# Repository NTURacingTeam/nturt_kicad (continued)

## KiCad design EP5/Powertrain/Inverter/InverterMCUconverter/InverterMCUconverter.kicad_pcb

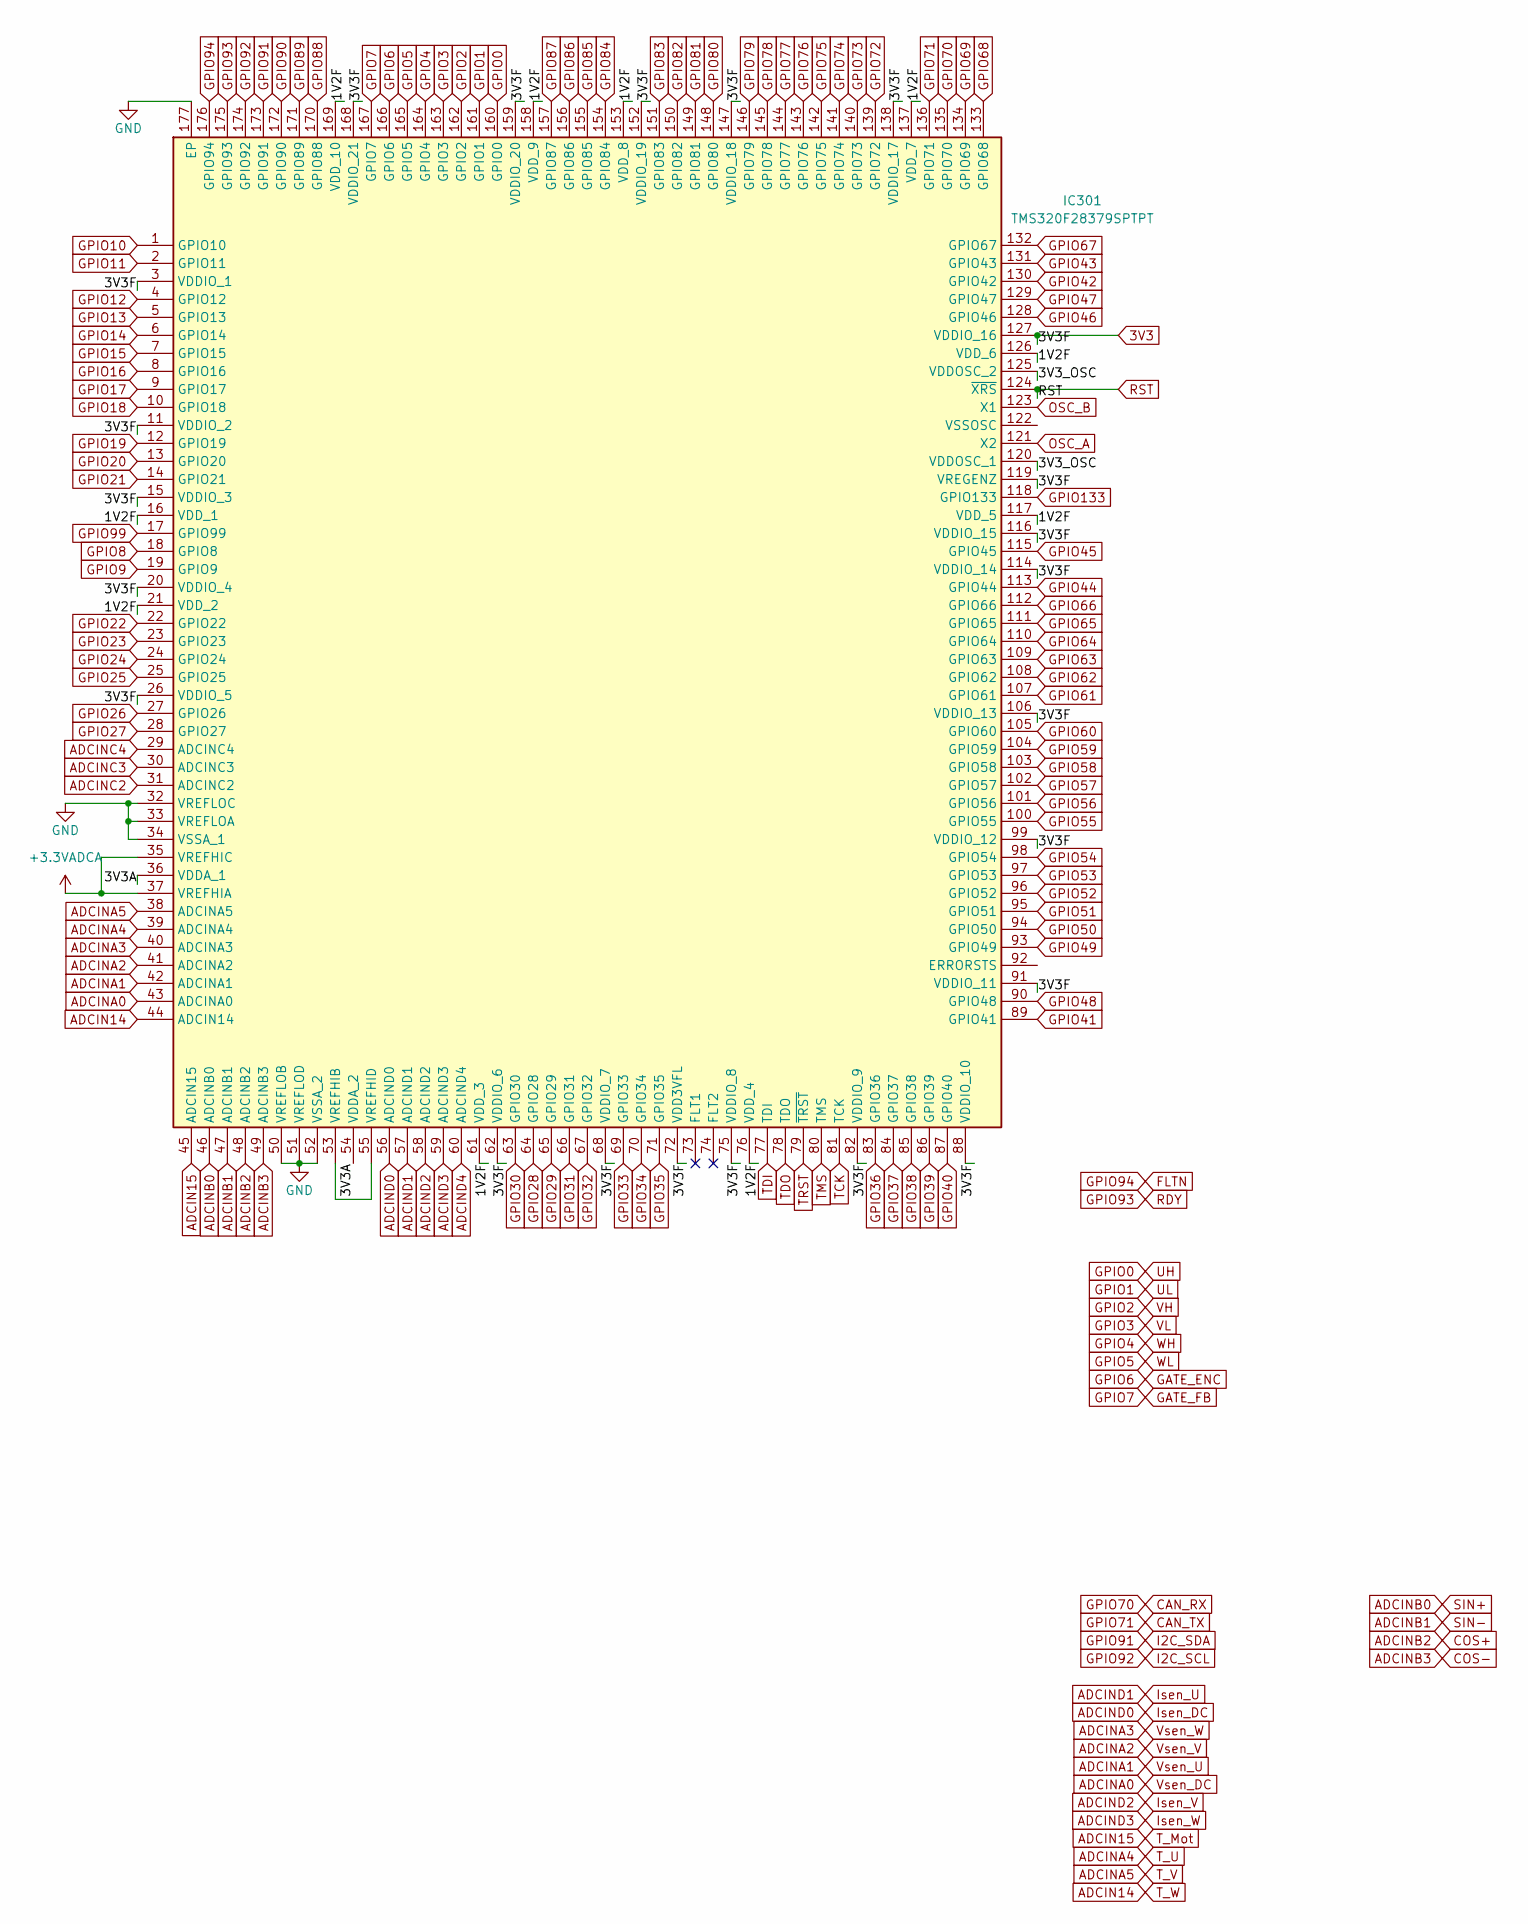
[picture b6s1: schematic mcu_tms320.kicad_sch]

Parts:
IC301: TMS320F28379SPTPT; QFP50P2600X2600X160-177N; Mouser Part Number 595-TMS32028379SPTPT

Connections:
3V3: IC301.3 (VDDIO_1), IC301.11 (VDDIO_2), IC301.15 (VDDIO_3), IC301.20 (VDDIO_4), IC301.26 (VDDIO_5), IC301.62 (VDDIO_6), IC301.68 (VDDIO_7), IC301.72 (VDD3VFL), IC301.75 (VDDIO_8), IC301.82 (VDDIO_9), IC301.88 (VDDIO_10), IC301.91 (VDDIO_11), IC301.99 (VDDIO_12), IC301.106 (VDDIO_13), IC301.114 (VDDIO_14), IC301.116 (VDDIO_15), IC301.119 (VREGENZ), IC301.127 (VDDIO_16), IC301.138 (VDDIO_17), IC301.147 (VDDIO_18), IC301.152 (VDDIO_19), IC301.159 (VDDIO_20), IC301.168 (VDDIO_21); also elsewhere on the board
+3.3VADCA: IC301.35 (VREFHIC), IC301.37 (VREFHIA)
/TMS320/1V2F: IC301.16 (VDD_1), IC301.21 (VDD_2), IC301.61 (VDD_3), IC301.76 (VDD_4), IC301.117 (VDD_5), IC301.126 (VDD_6), IC301.137 (VDD_7), IC301.153 (VDD_8), IC301.158 (VDD_9), IC301.169 (VDD_10)
/TMS320/3V3A: IC301.36 (VDDA_1), IC301.54 (VDDA_2)
/TMS320/3V3_OSC: IC301.120 (VDDOSC_1), IC301.125 (VDDOSC_2)
ADCIN14: IC301.44 (ADCIN14); also elsewhere on the board
ADCIN15: IC301.45 (ADCIN15); also elsewhere on the board
ADCINA0: IC301.43 (ADCINA0); also elsewhere on the board
ADCINA1: IC301.42 (ADCINA1); also elsewhere on the board
ADCINA2: IC301.41 (ADCINA2); also elsewhere on the board
ADCINA3: IC301.40 (ADCINA3); also elsewhere on the board
ADCINA4: IC301.39 (ADCINA4); also elsewhere on the board
ADCINA5: IC301.38 (ADCINA5); also elsewhere on the board
ADCINB0: IC301.46 (ADCINB0)
ADCINB1: IC301.47 (ADCINB1)
ADCINB2: IC301.48 (ADCINB2)
ADCINB3: IC301.49 (ADCINB3)
ADCINC2: IC301.31 (ADCINC2)
ADCINC3: IC301.30 (ADCINC3)
ADCINC4: IC301.29 (ADCINC4)
ADCIND0: IC301.56 (ADCIND0); also elsewhere on the board
ADCIND1: IC301.57 (ADCIND1); also elsewhere on the board
ADCIND2: IC301.58 (ADCIND2); also elsewhere on the board
ADCIND3: IC301.59 (ADCIND3); also elsewhere on the board
ADCIND4: IC301.60 (ADCIND4)
CAN_RX: IC301.135 (GPIO70); also elsewhere on the board
CAN_TX: IC301.136 (GPIO71); also elsewhere on the board
FLTN: IC301.176 (GPIO94); also elsewhere on the board
GATE_ENC: IC301.166 (GPIO6); also elsewhere on the board
GATE_FB: IC301.167 (GPIO7); also elsewhere on the board
GND: IC301.32 (VREFLOC), IC301.33 (VREFLOA), IC301.34 (VSSA_1), IC301.50 (VREFLOB), IC301.51 (VREFLOD), IC301.52 (VSSA_2), IC301.177 (EP); also elsewhere on the board
GPIO0: IC301.160 (GPIO0); also elsewhere on the board
GPIO1: IC301.161 (GPIO1); also elsewhere on the board
GPIO2: IC301.162 (GPIO2); also elsewhere on the board
GPIO3: IC301.163 (GPIO3); also elsewhere on the board
GPIO4: IC301.164 (GPIO4); also elsewhere on the board
GPIO5: IC301.165 (GPIO5); also elsewhere on the board
GPIO8: IC301.18 (GPIO8)
GPIO9: IC301.19 (GPIO9)
GPIO10: IC301.1 (GPIO10)
GPIO11: IC301.2 (GPIO11)
GPIO12: IC301.4 (GPIO12)
GPIO13: IC301.5 (GPIO13)
GPIO14: IC301.6 (GPIO14)
GPIO15: IC301.7 (GPIO15)
GPIO16: IC301.8 (GPIO16)
GPIO17: IC301.9 (GPIO17)
GPIO18: IC301.10 (GPIO18)
GPIO19: IC301.12 (GPIO19)
GPIO20: IC301.13 (GPIO20)
GPIO21: IC301.14 (GPIO21)
GPIO22: IC301.22 (GPIO22)
GPIO23: IC301.23 (GPIO23)
GPIO24: IC301.24 (GPIO24)
GPIO25: IC301.25 (GPIO25)
GPIO26: IC301.27 (GPIO26)
GPIO27: IC301.28 (GPIO27)
GPIO28: IC301.64 (GPIO28)
GPIO29: IC301.65 (GPIO29)
GPIO30: IC301.63 (GPIO30)
GPIO31: IC301.66 (GPIO31)
GPIO32: IC301.67 (GPIO32)
GPIO33: IC301.69 (GPIO33)
GPIO34: IC301.70 (GPIO34)
GPIO35: IC301.71 (GPIO35)
GPIO36: IC301.83 (GPIO36)
GPIO37: IC301.84 (GPIO37)
GPIO38: IC301.85 (GPIO38)
GPIO39: IC301.86 (GPIO39)
GPIO40: IC301.87 (GPIO40)
GPIO41: IC301.89 (GPIO41)
GPIO42: IC301.130 (GPIO42)
GPIO43: IC301.131 (GPIO43)
GPIO44: IC301.113 (GPIO44)
GPIO45: IC301.115 (GPIO45)
GPIO46: IC301.128 (GPIO46)
GPIO47: IC301.129 (GPIO47)
GPIO48: IC301.90 (GPIO48)
GPIO49: IC301.93 (GPIO49)
GPIO50: IC301.94 (GPIO50)
GPIO51: IC301.95 (GPIO51)
GPIO52: IC301.96 (GPIO52)
GPIO53: IC301.97 (GPIO53)
GPIO54: IC301.98 (GPIO54)
GPIO55: IC301.100 (GPIO55)
GPIO56: IC301.101 (GPIO56)
GPIO57: IC301.102 (GPIO57)
GPIO58: IC301.103 (GPIO58)
GPIO59: IC301.104 (GPIO59)
GPIO60: IC301.105 (GPIO60)
GPIO61: IC301.107 (GPIO61)
GPIO62: IC301.108 (GPIO62)
GPIO63: IC301.109 (GPIO63)
GPIO64: IC301.110 (GPIO64)
GPIO65: IC301.111 (GPIO65)
GPIO66: IC301.112 (GPIO66)
GPIO67: IC301.132 (GPIO67)
GPIO68: IC301.133 (GPIO68)
GPIO69: IC301.134 (GPIO69)
GPIO72: IC301.139 (GPIO72)
GPIO73: IC301.140 (GPIO73)
GPIO74: IC301.141 (GPIO74)
GPIO75: IC301.142 (GPIO75)
GPIO76: IC301.143 (GPIO76)
GPIO77: IC301.144 (GPIO77)
GPIO78: IC301.145 (GPIO78)
GPIO79: IC301.146 (GPIO79)
GPIO80: IC301.148 (GPIO80)
GPIO81: IC301.149 (GPIO81)
GPIO82: IC301.150 (GPIO82)
GPIO83: IC301.151 (GPIO83)
GPIO84: IC301.154 (GPIO84)
GPIO85: IC301.155 (GPIO85)
GPIO86: IC301.156 (GPIO86)
GPIO87: IC301.157 (GPIO87)
GPIO88: IC301.170 (GPIO88)
GPIO89: IC301.171 (GPIO89)
GPIO90: IC301.172 (GPIO90)
GPIO91: IC301.173 (GPIO91); also elsewhere on the board
GPIO92: IC301.174 (GPIO92); also elsewhere on the board
GPIO93: IC301.175 (GPIO93); also elsewhere on the board
GPIO99: IC301.17 (GPIO99)
GPIO133: IC301.118 (GPIO133)
unnamed: IC301.53 (VREFHIB), IC301.55 (VREFHID)
OSC_A: IC301.121 (X2); also elsewhere on the board
OSC_B: IC301.123 (X1); also elsewhere on the board
RST: IC301.124 (~XRS)
TCK: IC301.81 (TCK)
TDI: IC301.77 (TDI)
TDO: IC301.78 (TDO)
TMS: IC301.80 (TMS)
TRST: IC301.79 (~TRST)

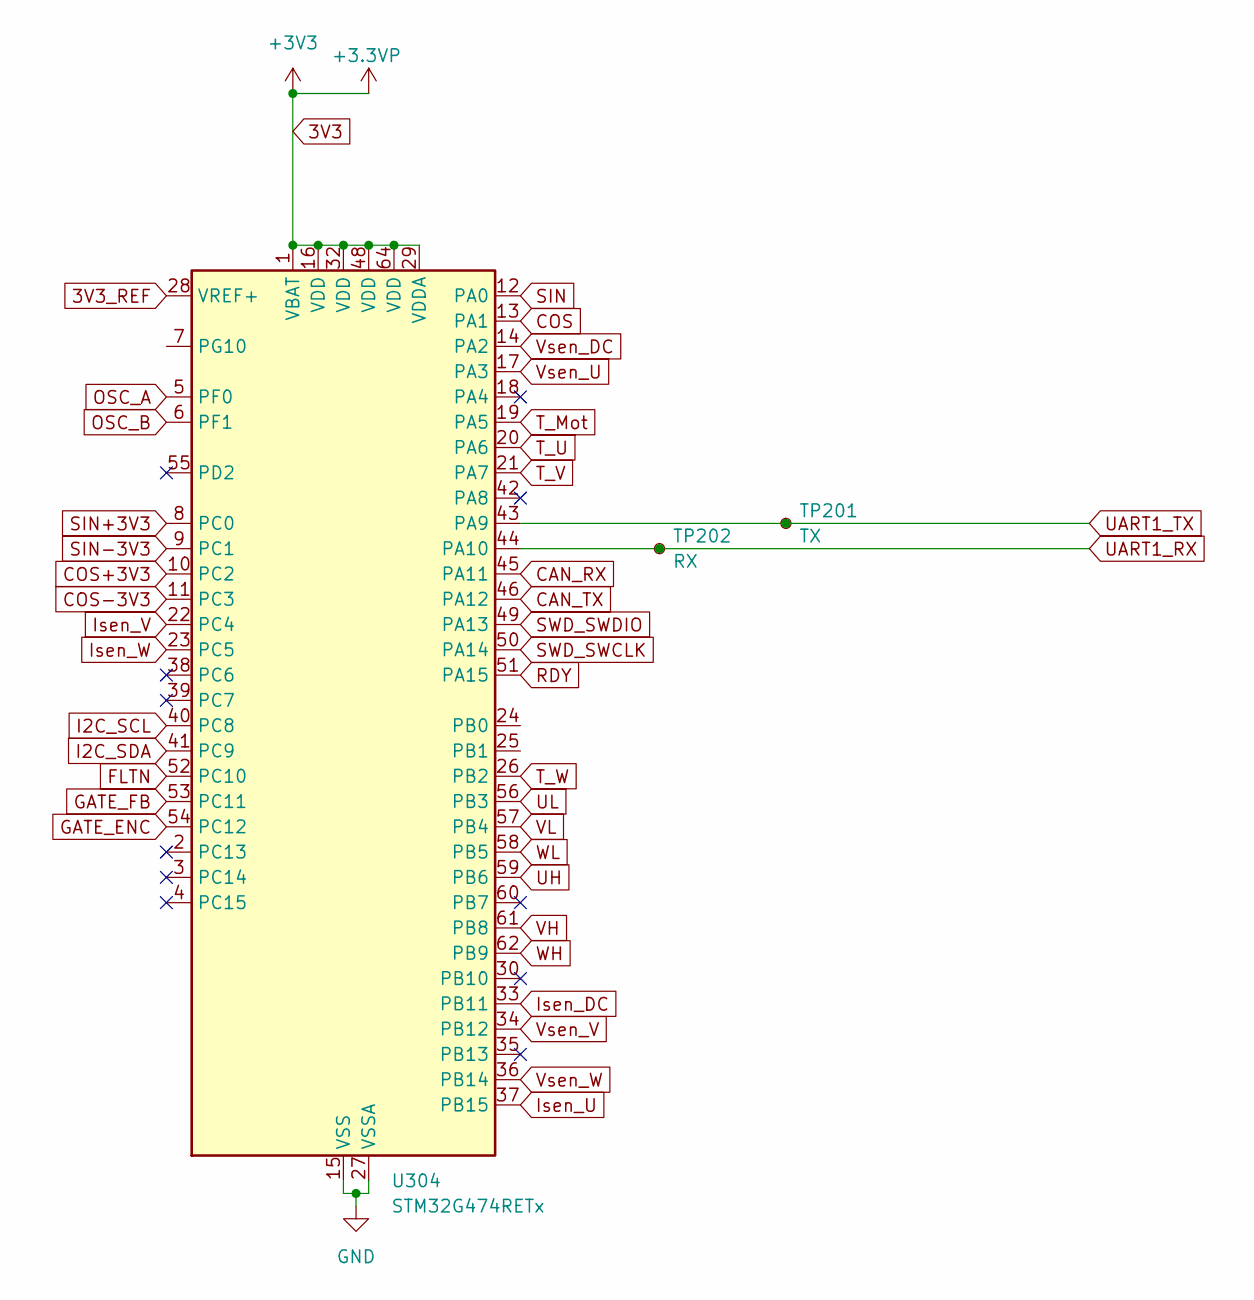
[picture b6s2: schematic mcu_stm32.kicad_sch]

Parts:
TP201: TX; TestPoint_Pad_D1.0mm
TP202: RX; TestPoint_Pad_D1.0mm
U304: STM32G474RETx; LQFP-64_10x10mm_P0.5mm

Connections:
3V3: U304.1 (VBAT), U304.16 (VDD), U304.29 (VDDA), U304.32 (VDD), U304.48 (VDD), U304.64 (VDD); also elsewhere on the board
3V3_REF: U304.28 (VREF+)
ADCIN14: U304.26 (PB2); also elsewhere on the board
ADCIN15: U304.19 (PA5); also elsewhere on the board
ADCINA0: U304.14 (PA2); also elsewhere on the board
ADCINA1: U304.17 (PA3); also elsewhere on the board
ADCINA2: U304.34 (PB12); also elsewhere on the board
ADCINA3: U304.36 (PB14); also elsewhere on the board
ADCINA4: U304.20 (PA6); also elsewhere on the board
ADCINA5: U304.21 (PA7); also elsewhere on the board
ADCIND0: U304.33 (PB11); also elsewhere on the board
ADCIND1: U304.37 (PB15); also elsewhere on the board
ADCIND2: U304.22 (PC4); also elsewhere on the board
ADCIND3: U304.23 (PC5); also elsewhere on the board
CAN_RX: U304.45 (PA11); also elsewhere on the board
CAN_TX: U304.46 (PA12); also elsewhere on the board
COS: U304.13 (PA1)
COS+3V3: U304.10 (PC2)
COS-3V3: U304.11 (PC3)
FLTN: U304.52 (PC10); also elsewhere on the board
GATE_ENC: U304.54 (PC12); also elsewhere on the board
GATE_FB: U304.53 (PC11); also elsewhere on the board
GND: U304.15 (VSS), U304.27 (VSSA), U304.31 (VSS), U304.47 (VSS), U304.63 (VSS); also elsewhere on the board
GPIO0: U304.59 (PB6); also elsewhere on the board
GPIO1: U304.56 (PB3); also elsewhere on the board
GPIO2: U304.61 (PB8); also elsewhere on the board
GPIO3: U304.57 (PB4); also elsewhere on the board
GPIO4: U304.62 (PB9); also elsewhere on the board
GPIO5: U304.58 (PB5); also elsewhere on the board
GPIO91: U304.41 (PC9); also elsewhere on the board
GPIO92: U304.40 (PC8); also elsewhere on the board
GPIO93: U304.51 (PA15); also elsewhere on the board
OSC_A: U304.5 (PF0); also elsewhere on the board
OSC_B: U304.6 (PF1); also elsewhere on the board
SIN: U304.12 (PA0)
SIN+3V3: U304.8 (PC0)
SIN-3V3: U304.9 (PC1)
SWD_SWCLK: U304.50 (PA14)
SWD_SWDIO: U304.49 (PA13)
UART1_RX: TP202.1, U304.44 (PA10)
UART1_TX: TP201.1, U304.43 (PA9)

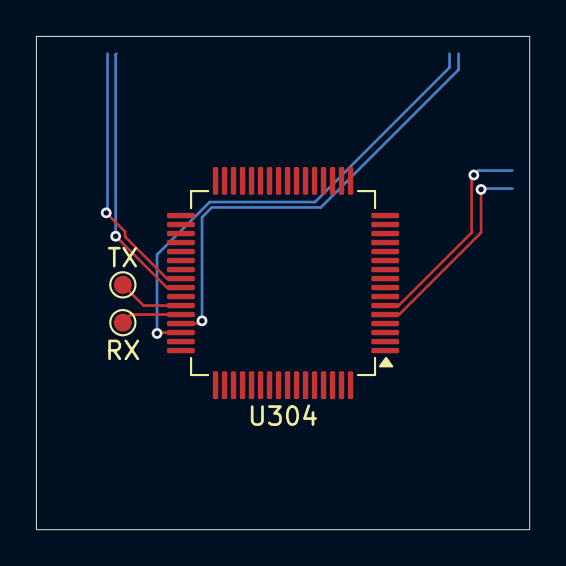
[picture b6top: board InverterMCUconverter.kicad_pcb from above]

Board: 2 copper layers, 27.4 x 27.4 mm, 4 parts (1 on the bottom side), 37 nets.

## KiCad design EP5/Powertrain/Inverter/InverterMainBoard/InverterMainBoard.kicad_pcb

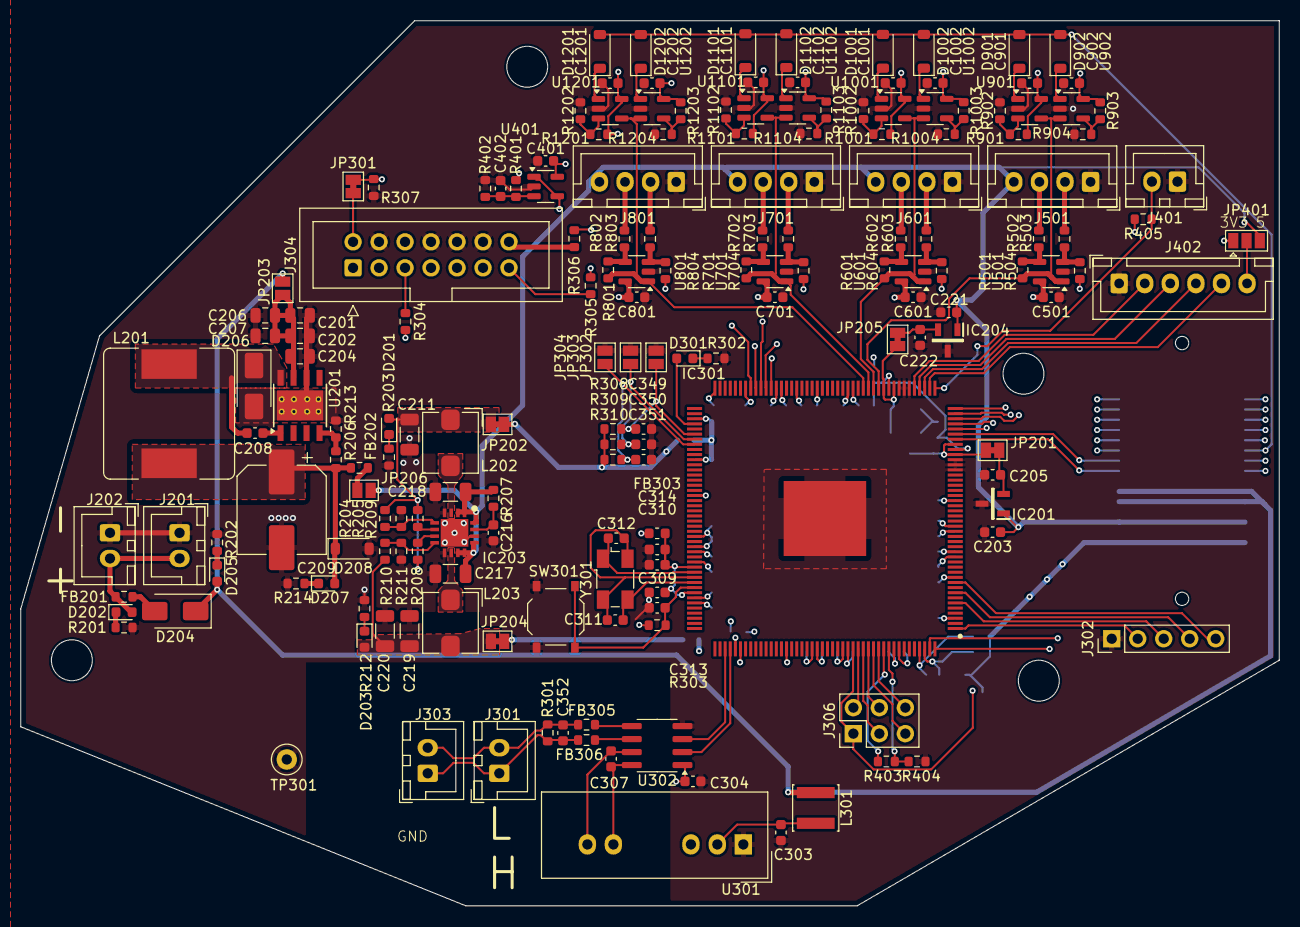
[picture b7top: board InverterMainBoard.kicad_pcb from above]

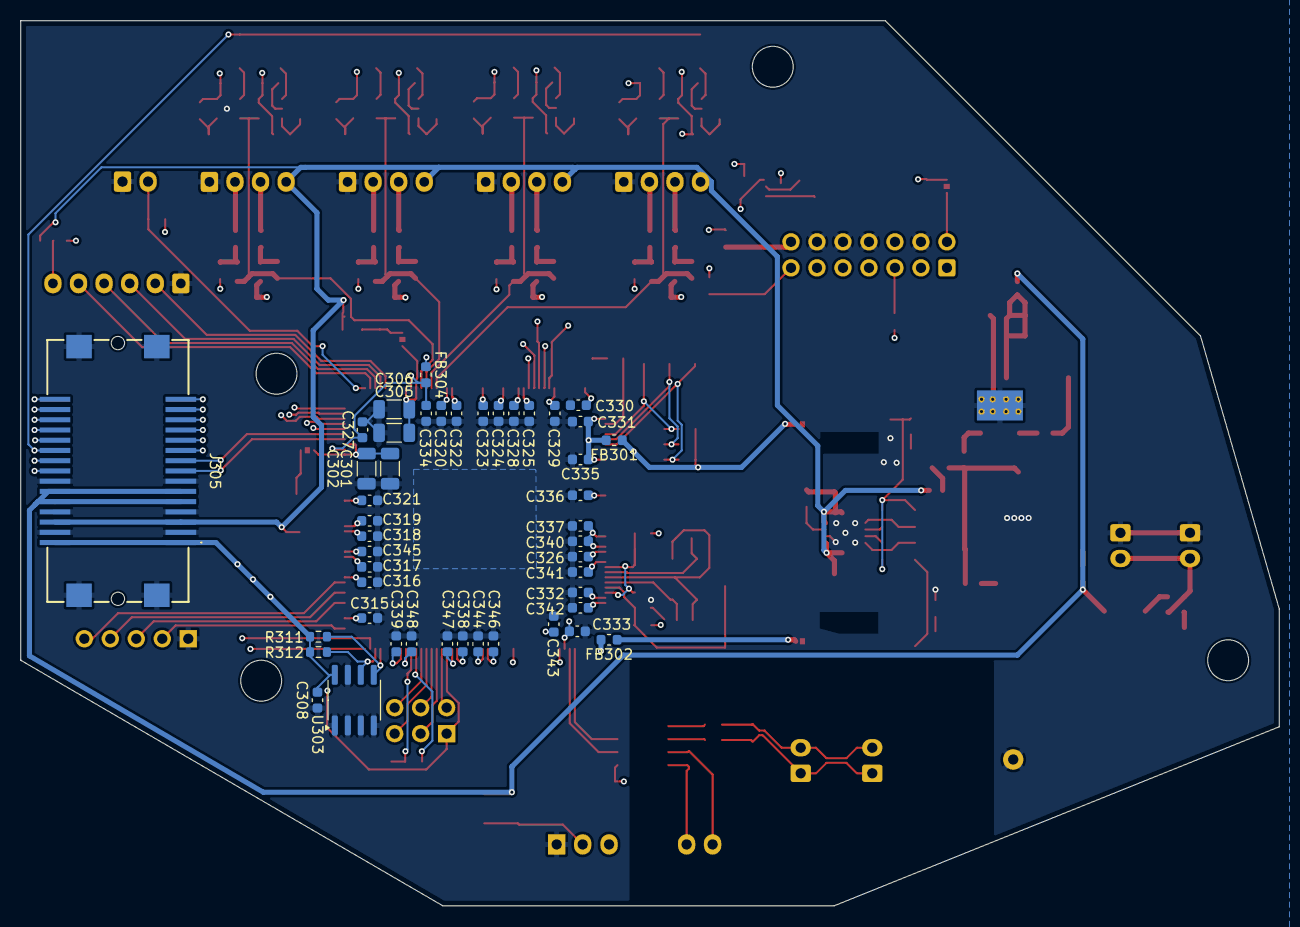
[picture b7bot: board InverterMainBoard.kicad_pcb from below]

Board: 4 copper layers, 123.0 x 86.5 mm, 228 parts (46 on the bottom side), 129 nets.

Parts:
C201, C202, C204, C206, C207: 2.2u 50V; C_0805_2012Metric
C203, C205, C216, C221, C222: 0.47u; C_0603_1608Metric
C208: 10n; C_0603_1608Metric
C209: 220u; CP_Elec_8x10.5
C211, C217, C218, C219, C220, C301, C302, C305, C306: 22u; C_1206_3216Metric
C303: 330n; C_0603_1608Metric
C304, C307, C309, C310, C313, C315, C316, C317, C318, C321, C322, C323, C324, C328, C329, C330, C331, C335, C336, C337, C340, C341, C342, C343, C346, C347, C348, C349, C350, C351, C352, C401, C402, C501, C601, C701, C801, C901, C902, C1001, C1002, C1101, C1102, C1201, C1202: 0.1u; C_0603_1608Metric
C308: 1u 10V; C_0603_1608Metric
C311, C312: 36p; C_0603_1608Metric
C314, C319, C320, C325, C326, C327, C332, C333, C334, C338, C339, C344, C345: 2.2u; C_0603_1608Metric
D201: 3V3_PG; LED_0603_1608Metric
D202: RED; LED_0603_1608Metric
D203: 1V2_PG; LED_0603_1608Metric
D204, D206: SS54; D_SMA
D205: Green; LED_0603_1608Metric
D207: 5VGood; LED_0603_1608Metric
D208: 5.1V; D_SOD-123
D301: ERROR; LED_0603_1608Metric
D901, D902, D1001, D1002, D1101, D1102, D1201, D1202: 1N4148W; D_SOD-123
FB201, FB202, FB305, FB306: 220; R_0603_1608Metric
FB301, FB302: BLM18KG221SH1D; L_0603_1608Metric
FB303, FB304: 74279228600; L_0603_1608Metric
H101, H102, H103, H104: MountingHole; MountingHole_4mm
IC201, IC204: REF3133AQDBZRQ1; SOT95P237X112-3N
IC203: LM26420Q1XSQX_NOPB; QFN65P400X400X80-17N
IC301: TMS320F28379SPTPT; QFP50P2600X2600X160-177N
J201, J202: PWR_IN; JST_XH_B2B-XH-A_1x02_P2.50mm_Vertical
J301, J303: CAN; JST_XH_B2B-XH-A_1x02_P2.50mm_Vertical
J302: PWMDAC; PinHeader_1x05_P2.54mm_Vertical
J304: JTAG; IDC-Header_2x07_P2.54mm_Vertical
J305: FX26-30P-1SV; FX2630P1SV
J306: Conn_02x03_Odd_Even; PinHeader_2x03_P2.54mm_Vertical
J401: T_Mot; JST_XH_B2B-XH-A_1x02_P2.50mm_Vertical
J402: Encoder; JST_XH_B6B-XH-A_1x06_P2.50mm_Vertical
J501, J601, J701, J801: ISen; JST_XH_B4B-XH-A_1x04_P2.50mm_Vertical
JP201, JP205: 3V3ADC_Cut; SolderJumper-2_P1.3mm_Bridged_Pad1.0x1.5mm
JP202: 3V3P_Cut; SolderJumper-2_P1.3mm_Bridged_Pad1.0x1.5mm
JP203: VB_5V; SolderJumper-2_P1.3mm_Open_Pad1.0x1.5mm
JP204: 1V2_Cut; SolderJumper-2_P1.3mm_Bridged_Pad1.0x1.5mm
JP206: SW_5V; SolderJumper-2_P1.3mm_Open_Pad1.0x1.5mm
JP301: TRST; SolderJumper-2_P1.3mm_Bridged_Pad1.0x1.5mm
JP302: 50; SolderJumper-2_P1.3mm_Open_Pad1.0x1.5mm
JP303: 51; SolderJumper-2_P1.3mm_Open_Pad1.0x1.5mm
JP304: 52; SolderJumper-2_P1.3mm_Open_Pad1.0x1.5mm
JP401: SolderJumper_3_Open; SolderJumper-3_P1.3mm_Open_Pad1.0x1.5mm
L201: 22uH; L_Bourns_SRR1260
L202, L203: SRP5030WA-1R0M; L_Bourns_SRP5030T
L301: 500u; L_Changjiang_FNR4030S
R201, R202: 5k; R_0603_1608Metric
R203, R302: 1.5k; R_0603_1608Metric
R204: 31.6k; R_0603_1608Metric
R205, R206, R211, R311, R312, R401, R402, R901, R904, R1001, R1004, R1101, R1104, R1201, R1204: 10k; R_0603_1608Metric
R207: 4.99; R_0603_1608Metric
R208, R209: 49.9k; R_0603_1608Metric
R210, R303, R308, R309, R310: 4.99k; R_0603_1608Metric
R212: 10; R_0603_1608Metric
R213: 3.24k; R_0603_1608Metric
R214: 2k; R_0603_1608Metric
R301: 120; R_0603_1608Metric
R304: 100; R_0603_1608Metric
R305, R306: 4.7k; R_0603_1608Metric
R307: 2.2k; R_0603_1608Metric
R403, R502, R503, R602, R603, R702, R703, R802, R803: 20k; R_0603_1608Metric
R404: 2Meg; R_0603_1608Metric
R405: 1k/1%; R_0603_1608Metric
R501, R504, R601, R604, R701, R704, R801, R804: 15k; R_0603_1608Metric
R902, R903, R1002, R1003, R1102, R1103, R1202, R1203: 45.3k; R_0603_1608Metric
SW301: RST; SW_Push_1P1T_XKB_TS-1187A
TP301: GND; TestPoint_Loop_D1.80mm_Drill1.0mm_Beaded
U201: TPS5430DDA; TI_SO-PowerPAD-8_ThermalVias
U301: NCS1S2405SC; Converter_DCDC_Murata_NCS1SxxxxSC_THT
U302: ISO1044BD; SOIC-8_3.9x4.9mm_P1.27mm
U303: CAT24C256; SOIC-8_3.9x4.9mm_P1.27mm
U401, U501, U601, U701, U801: OPA340NA; SOT-23-5
U901, U902, U1001, U1002, U1101, U1102, U1201, U1202: LMV7219M5; SOT-23-5
Y301: ABM3BAIG-10.000MHZ-12-1Z-T; Crystal_SMD_Abracon_ABM3B-4Pin_5.0x3.2mm

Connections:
1V65: R504.1, R604.1, R704.1, R804.1, U401.1, U401.4 (-)
3V3_Good: IC203.6 (PG1), R209.1
+1V2: FB302.1, JP204.2 (B)
+3.3VADCA: C301.1, C302.1, IC301.35 (VREFHIC), IC301.37 (VREFHIA), JP201.2 (B)
+3.3VADCB: C305.1, C306.1, IC301.53 (VREFHIB), IC301.55 (VREFHID), JP205.2 (B)
+3.3VP: C304.2, C308.1, C401.2, C501.2, C601.2, C701.2, C801.2, C901.2, C902.2, C1001.2, C1002.2, C1101.2, C1102.2, C1201.2, C1202.2, FB301.1, FB303.1, FB304.1, J305.1, J305.2, JP202.2 (B), JP401.1 (A), R303.2, R304.2, R305.2, R306.1, R308.2, R309.2, R310.2, R311.2, R312.2, R401.1, R405.2, R901.2, R903.2, R1001.2, R1003.2, R1101.2, R1103.2, R1201.2, R1203.2, U302.1 (VCC1), U303.8 (VCC), U401.5 (V+), U501.5 (V+), U601.5 (V+), U701.5 (V+), U801.5 (V+), U901.5 (V+), U902.5 (V+), U1001.5 (V+), U1002.5 (V+), U1101.5 (V+), U1102.5 (V+), U1201.5 (V+), U1202.5 (V+)
+5V: C203.1, C217.1, C218.1, C221.1, IC201.1 (IN), IC203.1 (VIND1_1), IC203.2 (VIND1_2), IC203.11 (VIND2_1), IC203.12 (VIND2_2), IC203.13 (EN2), IC203.16 (EN1), IC204.1 (IN), J305.5, J305.6, J501.4, J601.4, J701.4, J801.4, JP206.2 (B), JP401.3 (B), R207.1
/Mcu/1V2F: C319.1, C320.1, C325.1, C326.1, C332.1, C333.1, C338.1, C339.1, C344.1, C345.1, FB302.2, IC301.16 (VDD_1), IC301.21 (VDD_2), IC301.61 (VDD_3), IC301.76 (VDD_4), IC301.117 (VDD_5), IC301.126 (VDD_6), IC301.137 (VDD_7), IC301.153 (VDD_8), IC301.158 (VDD_9), IC301.169 (VDD_10)
/Mcu/3V3A: C327.1, C334.1, FB304.2, IC301.36 (VDDA_1), IC301.54 (VDDA_2)
/Mcu/3V3F: C315.1, C316.1, C317.1, C318.1, C321.1, C322.1, C323.1, C324.1, C328.1, C329.1, C330.1, C331.1, C335.1, C336.1, C337.1, C340.1, C341.1, C342.1, C343.1, C346.1, C347.1, C348.1, FB301.2, IC301.3 (VDDIO_1), IC301.11 (VDDIO_2), IC301.15 (VDDIO_3), IC301.20 (VDDIO_4), IC301.26 (VDDIO_5), IC301.62 (VDDIO_6), IC301.68 (VDDIO_7), IC301.72 (VDD3VFL), IC301.75 (VDDIO_8), IC301.82 (VDDIO_9), IC301.88 (VDDIO_10), IC301.91 (VDDIO_11), IC301.99 (VDDIO_12), IC301.106 (VDDIO_13), IC301.114 (VDDIO_14), IC301.116 (VDDIO_15), IC301.119 (VREGENZ), IC301.127 (VDDIO_16), IC301.138 (VDDIO_17), IC301.147 (VDDIO_18), IC301.152 (VDDIO_19), IC301.159 (VDDIO_20), IC301.168 (VDDIO_21)
/Mcu/3V3_OSC: C309.1, C310.1, C314.1, FB303.2, IC301.120 (VDDOSC_1), IC301.125 (VDDOSC_2)
/Mcu/CANFN: C352.1, FB305.1, J301.2, J303.2, R301.2
/Mcu/CANFP: C352.2, FB306.2, J301.1, J303.1, R301.1
/Mcu/CANN: FB305.2, U302.5 (CANL)
/Mcu/CANP: FB306.1, U302.6 (CANH)
/Mcu/RST: C313.1, IC301.124 (~XRS), R303.1, SW301.1
ADCIN14: IC301.44 (ADCIN14), J305.30
ADCIN15: IC301.45 (ADCIN15), J401.2, R405.1
ADCINA0: IC301.43 (ADCINA0), J305.28
ADCINA1: IC301.42 (ADCINA1), J305.26
ADCINA2: IC301.41 (ADCINA2), J305.24
ADCINA3: IC301.40 (ADCINA3), J305.22
ADCINA4: IC301.39 (ADCINA4), J305.17
ADCINA5: IC301.38 (ADCINA5), J305.15
ADCINB0: IC301.46 (ADCINB0), J402.5
ADCINB1: IC301.47 (ADCINB1), J402.4
ADCINB2: IC301.48 (ADCINB2), J402.3
ADCINB3: IC301.49 (ADCINB3), J402.2
ADCIND0: IC301.56 (ADCIND0), R501.2, U501.1, U901.4 (-), U902.3 (+)
ADCIND1: IC301.57 (ADCIND1), R601.2, U601.1, U1001.4 (-), U1002.3 (+)
ADCIND2: IC301.58 (ADCIND2), R701.2, U701.1, U1101.4 (-), U1102.3 (+)
ADCIND3: IC301.59 (ADCIND3), R801.2, U801.1, U1201.4 (-), U1202.3 (+)
CAN_RX: IC301.135 (GPIO70), U302.3 (RXD)
CAN_TX: IC301.136 (GPIO71), U302.2 (TXD)
ENU: D901.2 (A), D902.2 (A), D1001.2 (A), D1002.2 (A), D1101.2 (A), D1102.2 (A), D1201.2 (A), D1202.2 (A), IC301.167 (GPIO7), J305.20, R403.1, R404.2
FLTN: IC301.176 (GPIO94), J305.16
GATE_ENC: IC301.166 (GPIO6), R403.2
GND: C201.2, C202.2, C203.2, C204.2, C205.2, C206.2, C207.2, C209.2, C211.2, C216.2, C217.2, C218.2, C219.2, C220.2, C221.2, C222.2, C301.2, C302.2, C303.2, C304.1, C305.2, C306.2, C308.2, C309.2, C310.2, C313.2, C314.2, C315.2, C316.2, C317.2, C318.2, C319.2, C320.2, C321.2, C322.2, C323.2, C324.2, C325.2, C326.2, C327.2, C328.2, C329.2, C330.2, C331.2, C332.2, C333.2, C334.2, C335.2, C336.2, C337.2, C338.2, C339.2, C340.2, C341.2, C342.2, C343.2, C344.2, C345.2, C346.2, C347.2, C348.2, C349.2, C350.2, C351.2, C401.1, C402.1, C501.1, C601.1, C701.1, C801.1, C901.1, C902.1, C1001.1, C1002.1, C1101.1, C1102.1, C1201.1, C1202.1, D206.2 (A), D208.2 (A), IC201.3 (GND), IC203.4 (PGND1), IC203.9 (PGND2), IC203.14 (AGND), IC203.17 (EP), IC204.3 (GND), IC301.32 (VREFLOC), IC301.33 (VREFLOA), IC301.34 (VSSA_1), IC301.50 (VREFLOB), IC301.51 (VREFLOD), IC301.52 (VSSA_2), IC301.177 (EP), J201.1, J202.1, J302.1, J304.4, J304.8, J304.10, J304.12, J305.3, J305.4, J305.7, J305.8, J305.13, J305.14, J305.MP1, J305.MP2, J305.MP3, J305.MP4, J401.1, J402.1, J501.1, J601.1, J701.1, J801.1, JP302.2 (B), JP303.2 (B), JP304.2 (B), R201.2, R202.2, R203.1, R205.1, R211.1, R212.1, R213.1, R214.2, R302.1, R307.2, R402.1, R404.1, R902.1, R904.1, R1002.1, R1004.1, R1102.1, R1104.1, R1202.1, R1204.1, SW301.2, TP301.1, U201.6 (GND), U201.9 (GNDPAD), U301.1 (-VIN), U302.4 (GND1), U303.1 (A0), U303.2 (A1), U303.3 (A2), U303.4 (GND), U303.7 (WP), U401.2 (V-), U501.2 (V-), U601.2 (V-), U701.2 (V-), U801.2 (V-), U901.2 (V-), U902.2 (V-), U1001.2 (V-), U1002.2 (V-), U1101.2 (V-), U1102.2 (V-), U1201.2 (V-), U1202.2 (V-)
GPIO0: IC301.160 (GPIO0), J305.25, J306.1
GPIO1: IC301.161 (GPIO1), J305.23, J306.2
GPIO2: IC301.162 (GPIO2), J305.27, J306.3
GPIO3: IC301.163 (GPIO3), J305.21, J306.4
GPIO4: IC301.164 (GPIO4), J305.29, J306.5
GPIO5: IC301.165 (GPIO5), J305.19, J306.6
GPIO10: IC301.1 (GPIO10), J302.2
GPIO14: IC301.6 (GPIO14), J302.3
GPIO16: IC301.8 (GPIO16), J302.4
GPIO18: IC301.10 (GPIO18), J302.5
GPIO50: C349.1, IC301.94 (GPIO50), JP302.1 (A), R308.1
GPIO51: C350.1, IC301.95 (GPIO51), JP303.1 (A), R309.1
GPIO52: C351.1, IC301.96 (GPIO52), JP304.1 (A), R310.1
GPIO91: IC301.173 (GPIO91), R311.1, U303.5 (SDA)
GPIO92: IC301.174 (GPIO92), R312.1, U303.6 (SCL)
GPIO93: IC301.175 (GPIO93), J305.18
unnamed: C211.1, D201.2 (A), JP202.1 (A), L202.1, R204.2, R208.2, R209.2
unnamed: D201.1 (K), R203.2
unnamed: D202.2 (A), FB201.1, J201.2, J202.2
unnamed: D202.1 (K), R201.1
unnamed: C219.1, C220.1, D203.2 (A), JP204.1 (A), L203.2, R210.2
unnamed: D203.1 (K), R212.2
unnamed: D204.2 (A), FB201.2
unnamed: D205.1 (K), R202.1
unnamed: C208.2, D206.1 (K), L201.1, U201.8 (PH)
unnamed: C209.1, D207.2 (A), D208.1 (K), FB202.1, L201.2, R206.2
unnamed: D207.1 (K), R214.1
unnamed: D301.2 (A), IC301.92 (ERRORSTS)
unnamed: D301.1 (K), R302.2
unnamed: D901.1 (K), U901.1
unnamed: D902.1 (K), U902.1
unnamed: D1001.1 (K), U1001.1
unnamed: D1002.1 (K), U1002.1
unnamed: D1101.1 (K), U1101.1
unnamed: D1102.1 (K), U1102.1
unnamed: D1201.1 (K), U1201.1
unnamed: D1202.1 (K), U1202.1
unnamed: C205.1, IC201.2 (OUT), JP201.1 (A)
unnamed: IC203.5 (FB1), R204.1, R205.2
unnamed: IC203.8 (FB2), R210.1, R211.2
unnamed: IC203.7 (PG2), R208.1
unnamed: IC203.3 (SW1), L202.2
unnamed: IC203.10 (SW2), L203.1
unnamed: C216.1, IC203.15 (VINC), R207.2
unnamed: C222.1, IC204.2 (OUT), JP205.1 (A)
unnamed: C311.2, C312.2, IC301.122 (VSSOSC), Y301.2, Y301.4
unnamed: C311.1, IC301.123 (X1), Y301.3
unnamed: C312.1, IC301.121 (X2), Y301.1
unnamed: J304.2, JP301.1 (A)
unnamed: J304.5, R304.1
unnamed: J304.13, R305.1
unnamed: J304.14, R306.2
unnamed: J402.6, JP401.2 (C)
unnamed: J501.2, R503.1
unnamed: J501.3, R502.1
unnamed: J601.2, R603.1
unnamed: J601.3, R602.1
unnamed: J701.2, R703.1
unnamed: J701.3, R702.1
unnamed: J801.2, R803.1
unnamed: J801.3, R802.1
unnamed: C201.1, C202.1, C204.1, C206.1, C207.1, JP203.2 (B), U201.7 (VIN)
unnamed: FB202.2, JP206.1 (A)
unnamed: C208.1, U201.1 (BOOT)
unnamed: R206.1, R213.2, U201.4 (VSENSE)
unnamed: C303.1, L301.2, U301.2 (+VIN)
unnamed: C307.1, U301.6 (+VOUT), U302.8 (VCC2)
unnamed: C307.2, U301.7 (-VOUT), U302.7 (GND2)
unnamed: C402.2, R401.2, R402.2, U401.3 (+)
unnamed: R503.2, R504.2, U501.3 (+)
unnamed: R501.1, R502.2, U501.4 (-)
unnamed: R603.2, R604.2, U601.3 (+)
unnamed: R601.1, R602.2, U601.4 (-)
unnamed: R703.2, R704.2, U701.3 (+)
unnamed: R701.1, R702.2, U701.4 (-)
unnamed: R803.2, R804.2, U801.3 (+)
unnamed: R801.1, R802.2, U801.4 (-)
unnamed: R901.1, R902.2, U901.3 (+)
unnamed: R903.1, R904.2, U902.4 (-)
unnamed: R1001.1, R1002.2, U1001.3 (+)
unnamed: R1003.1, R1004.2, U1002.4 (-)
unnamed: R1101.1, R1102.2, U1101.3 (+)
unnamed: R1103.1, R1104.2, U1102.4 (-)
unnamed: R1201.1, R1202.2, U1201.3 (+)
unnamed: R1203.1, R1204.2, U1202.4 (-)
TCK: IC301.81 (TCK), J304.9, J304.11
TDI: IC301.77 (TDI), J304.3
TDO: IC301.78 (TDO), J304.7
TMS: IC301.80 (TMS), J304.1
TRST: IC301.79 (~TRST), JP301.2 (B), R307.1
VCC: D204.1 (K), D205.2 (A), J305.9, J305.10, J305.11, J305.12, JP203.1 (A), L301.1
